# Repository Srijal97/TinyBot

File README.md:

# TinyBot
Creating Really tiny robots of dimensions about 1x1x1cm using the ESP8285(ESP-01F) WiFi modules.

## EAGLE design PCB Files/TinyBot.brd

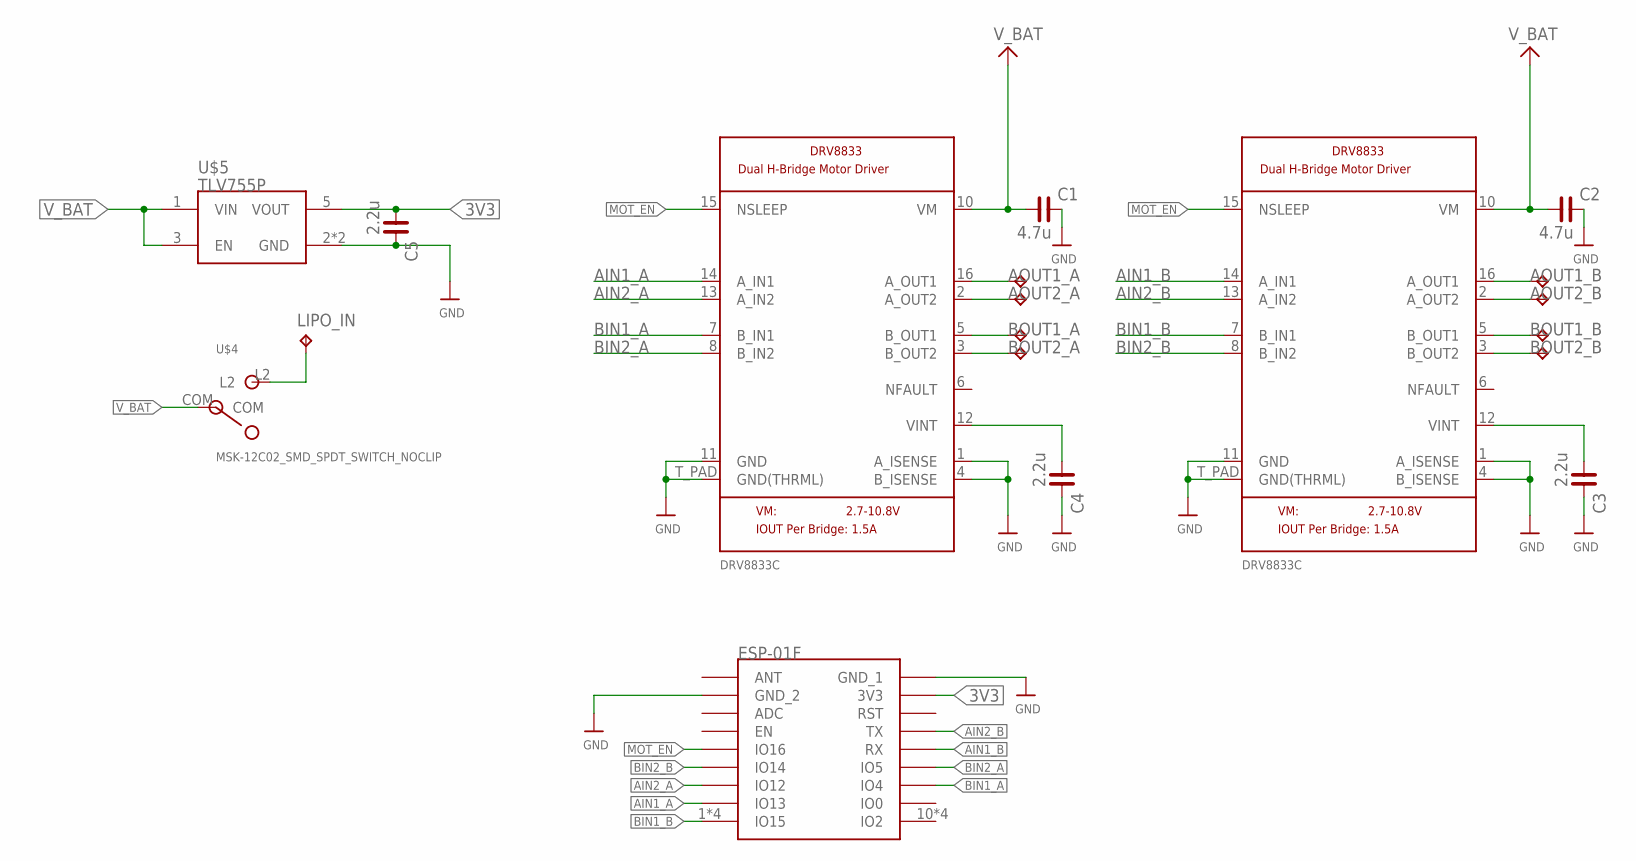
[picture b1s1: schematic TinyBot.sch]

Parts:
C1, C2: 4.7u; C0201
C3, C4, C5: 2.2u; C0201
LIPO_IN: TPTP11SQ; TP11SQ
TP1, TP2, TP3, TP4, TP5, TP6, TP7, TP8: TPTP07SQ; TP07SQ
U$1: ESP01F
U$4: MSK-12C02_SMD_SPDT_SWITCH_NOCLIP; MSK-12C02_NOCLIP
U$5: TLV755P; SOT23-5
U$11, U$16: DRV8833C; QFN16

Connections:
3V3: C5.1, U$1.17 (3V3), U$1.26 (3V3), U$1.44 (3V3), U$1.71 (3V3), U$5.5 (VOUT)
AIN1_A: U$1.2 (IO13), U$1.29 (IO13), U$1.47 (IO13), U$1.56 (IO13), U$11.14 (A_IN1)
AIN1_B: U$1.14 (RX), U$1.23 (RX), U$1.41 (RX), U$1.68 (RX), U$16.14 (A_IN1)
AIN2_A: U$1.3 (IO12), U$1.30 (IO12), U$1.48 (IO12), U$1.57 (IO12), U$11.13 (A_IN2)
AIN2_B: U$1.15 (TX), U$1.24 (TX), U$1.42 (TX), U$1.69 (TX), U$16.13 (A_IN2)
AOUT1_A: TP1.TP, U$11.16 (A_OUT1)
AOUT1_B: TP5.TP, U$16.16 (A_OUT1)
AOUT2_A: TP2.TP, U$11.2 (A_OUT2)
AOUT2_B: TP6.TP, U$16.2 (A_OUT2)
BIN1_A: U$1.12 (IO4), U$1.21 (IO4), U$1.39 (IO4), U$1.66 (IO4), U$11.7 (B_IN1)
BIN1_B: U$1.1 (IO15), U$1.28 (IO15), U$1.46 (IO15), U$1.55 (IO15), U$16.7 (B_IN1)
BIN2_A: U$1.13 (IO5), U$1.22 (IO5), U$1.40 (IO5), U$1.67 (IO5), U$11.8 (B_IN2)
BIN2_B: U$1.4 (IO14), U$1.31 (IO14), U$1.49 (IO14), U$1.58 (IO14), U$16.8 (B_IN2)
BOUT1_A: TP3.TP, U$11.5 (B_OUT1)
BOUT1_B: TP7.TP, U$16.5 (B_OUT1)
BOUT2_A: TP4.TP, U$11.3 (B_OUT2)
BOUT2_B: TP8.TP, U$16.3 (B_OUT2)
GND: C1.2, C2.2, C3.2, C4.2, C5.2, U$1.8 (GND_2), U$1.18 (GND_1), U$1.27 (GND_1), U$1.35 (GND_2), U$1.45 (GND_1), U$1.53 (GND_2), U$1.62 (GND_2), U$1.72 (GND_1), U$5.2 (GND), U$5.4 (GND), U$11.1 (A_ISENSE), U$11.4 (B_ISENSE), U$11.11 (GND), U$11.T_PAD (GND(THRML)), U$16.1 (A_ISENSE), U$16.4 (B_ISENSE), U$16.11 (GND), U$16.T_PAD (GND(THRML))
LIPO_IN: LIPO_IN.TP, U$4.L2
MOT_EN: U$1.5 (IO16), U$1.32 (IO16), U$1.50 (IO16), U$1.59 (IO16), U$11.15 (NSLEEP), U$16.15 (NSLEEP)
VINT_A: C4.1, U$11.12 (VINT)
VINT_B: C3.1, U$16.12 (VINT)
V_BAT: C1.1, C2.1, U$4.COM, U$5.1 (VIN), U$5.3 (EN), U$11.10 (VM), U$16.10 (VM)

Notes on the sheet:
V_BAT

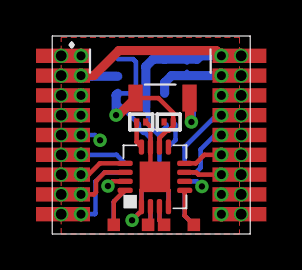
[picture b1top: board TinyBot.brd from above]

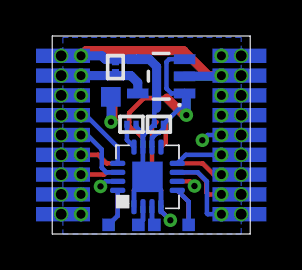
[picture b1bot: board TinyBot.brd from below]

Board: 2 copper layers, 11.0 x 11.0 mm, 19 parts (10 on the bottom side), 23 nets.

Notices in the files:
parts and their libraries:
SparkFun-IC-Power: Licensing: Creative Commons ShareAlike 4.0 International - https://creativecommons.org/licenses/by-sa/4.0
rc-master-smd: Copyright (C) 2007, Bob Starr
